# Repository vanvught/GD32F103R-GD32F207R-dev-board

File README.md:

See the latest here -> https://github.com/vanvught/GD32FxxxR-dev-board

-----------

# GD32F103R-GD32F207R-dev-board

This board can be used with the `GD32F103Rx` and the `GD32F207Rx` (Ethernet) MCU's. 

Please note that the crystal for the `GD32F207Rx` is `25MHz` and the crystal for the `GD32F103Rx` is `8MHz`.

The USB is power only.

The 2x13 header is pin compatible with the Orange Pi Zero and Raspberry Pi boards. 

<table>
	<tr><th colspan="6">2x13 Header</th></tr>
	<tr>
	<td colspan="2">3.3V PWR</td>
	<td>1</td>
	<td>2</td>
	<td colspan="2">5V PWR</td>
	</tr>
	<tr>
	<td>I2C0 SCA</td>
	<td>PB7</td>
	<td>3</td>
	<td>4</td>
	<td colspan="2">5V PWR</td>
	</tr>
	<tr>
	<td>I2C0 SCL</td>
	<td>PB6</td>
	<td>5</td>
	<td>6</td>
	<td colspan="2">GND</td>
	</tr>
	<tr>
	<td></td>
	<td>PA6</td>
	<td>7</td>
	<td>8</td>
	<td>PC10</td>
	<td>USART2 TX</td>
	</tr>
	<tr>
	<td colspan="2">GND</td>
	<td>9</td>
	<td>10</td>
	<td>PC11</td>
	<td>USART2 RX</td>
	</tr>
	<tr>
	<td>USART5 RX</td>
	<td>PC7</td>
	<td>11</td>
	<td>12</td>
	<td>PB10</td>
	<td></td>
	</tr>
	<tr>
	<td>USART5 TX</td>
	<td>PC6</td>
	<td>13</td>
	<td>14</td>
	<td colspan="2">GND</td>
	</tr>
	<tr>
	<td></td>
	<td>PB14</td>
	<td>15</td>
	<td>16</td>
	<td>PB15</td>
	<td></td>
	</tr>
	<tr>
	<td colspan="2">3.3V PWR</td>
	<td>17</td>
	<td>18</td>
	<td>PA13</td>
	<td>SWDIO</td>
	</tr>
	<tr>
	<td>SPI2 MOSI</td>
	<td>PB5</td>
	<td>19</td>
	<td>20</td>
	<td colspan="2">GND</td>
	</tr>
	<tr>
	<td>SPI2 MISO</td>
	<td>PB4</td>
	<td>21</td>
	<td>22</td>
	<td>PA11</td>
	<td></td>
	</tr>
	<tr>
	<td>SPI2 SCK</td>
	<td>PB3</td>
	<td>23</td>
	<td>24</td>
	<td>PA15</td>
	<td>SPI2 CS</td>
	</tr>
	<tr>
	<td colspan="2">GND</td>
	<td>25</td>
	<td>26</td>
	<td>PA14</td>
	<td>SWCLK</td>
	</tr>
</table>

<table>
	<tr><th colspan="3">1x13 Header</th></tr>
	<tr>
	<td>1</td>
	<td colspan="2">NC</td>
	</tr>
	<tr>
	<td>2</td>
	<td colspan="2">GND</td>
	</tr>
	<tr>
	<td>3</td>
	<td>PA14</td>
	<td>SWCLK</td>
	</tr>
	<tr>
	<td>4</td>
	<td colspan="2">GND</td>
	</tr>
	<tr>
	<td>5</td>
	<td>PA13</td>
	<td>SWDIO</td>
	</tr>
	<tr>
	<td>6</td>
	<td colspan="2">NRST</td>
	</tr>
	<tr>
	<td>7</td>
	<td>PA5</td>
	<td>DAC1</td>
	</tr>
	<tr>
	<td>8</td>
	<td>PA4</td>
	<td>DAC0</td>
	</tr>
	<tr>
	<td>9</td>
	<td>PC12</td>
	<td>UART4 TX</td>
	</tr>
	<tr>
	<td>10</td>
	<td>PD2</td>
	<td>UART4 RX</td>
	</tr>
	<tr>
	<td>11</td>
	<td colspan="2">NC</td>
	</tr>
	<tr>
	<td>12</td>
	<td>PA3</td>
	<td>ADC</td>
	</tr>
	<tr>
	<td>13</td>
	<td colspan="2">NC</td>
	</tr>
</table>

<table>
	<tr><th colspan="2">USART0 (ISP)</th></tr>
	<tr>
	<td>1</td>
	<td>GND</td>
	</tr>
	<tr>
	<td>2</td>
	<td>RX</td>
	</tr>
	<tr>
	<td>3</td>
	<td>TX</td>
	</tr>	
</table>

<table>
<head>
	<tr>
		<th colspan="2">LED's</th>
	</tr>
</head>
<tbody>
	<tr>
		<td>1</td>
		<td>PC0</td>
	</tr>
	<tr>
		<td>2</td>
		<td>PC2</td>
	</tr>
	<tr>
		<td>3</td>
		<td>PC3</td>
	</tr>
	<tr>
		<td>4</td>
		<td>3V3</td>
	</tr>	
</tbody>
</table>

<table>
	<tr><th colspan="4">2x7 Header</th></tr>
	<tr>
	<td>PB13</td>
	<td>1</td>
	<td>2</td>
	<td>NC</td>
	</tr>
	<tr>
	<td>PB11</td>
	<td>3</td>
	<td>4</td>
	<td>PB12</td>
	</tr>
	<tr>
	<td>PC4</td>
	<td>5</td>
	<td>6</td>
	<td>PC5</td>
	</tr>
	<tr>
	<td>PA1</td>
	<td>7</td>
	<td>8</td>
	<td>PA7</td>
	</tr>
	<tr>
	<td>PA2</td>
	<td>9</td>
	<td>10</td>
	<td>PC1</td>
	</tr>
	<tr>
	<td>GND</td>
	<td>11</td>
	<td>12</td>
	<td>GND</td>
	</tr>
	<tr>
	<td>3V3</td>
	<td>13</td>
	<td>14</td>
	<td>3V3</td>
	</tr>	
</table>

### GD32F207Rx (only)

<table>
<head>
	<tr>
		<th colspan="4">External-PHY</th>
	</tr>
</head>
<tbody>
	<tr>
		<td>RMII TXD1</td>
		<td>1</td>
		<td>2</td>
		<td>NC</td>
	</tr>
	<tr>
		<td>RMII TX_EN</td>
		<td>3</td>
		<td>4</td>
		<td>RMII TXD0</td>
	</tr>
	<tr>
		<td>RMII RXD0</td>
		<td>5</td>
		<td>6</td>
		<td>RMII RXD1</td>
	</tr>
	<tr>
		<td>RMII REF_CLK</td>
		<td>7</td>
		<td>8</td>
		<td>RMII CRS_DV</td>
	</tr>
	<tr>
		<td>MDIO</td>
		<td>9</td>
		<td>10</td>
		<td>MDC</td>
	</tr>
	<tr>
		<td>GND</td>
		<td>11</td>
		<td>12</td>
		<td>GND</td>
	</tr>
	<tr>
		<td>3V3</td>
		<td>13</td>
		<td>14</td>
		<td>3V3</td>
	</tr>		
</tbody>
</table>

[PayPal.Me Donate](https://paypal.me/AvanVught?locale.x=nl_NL)

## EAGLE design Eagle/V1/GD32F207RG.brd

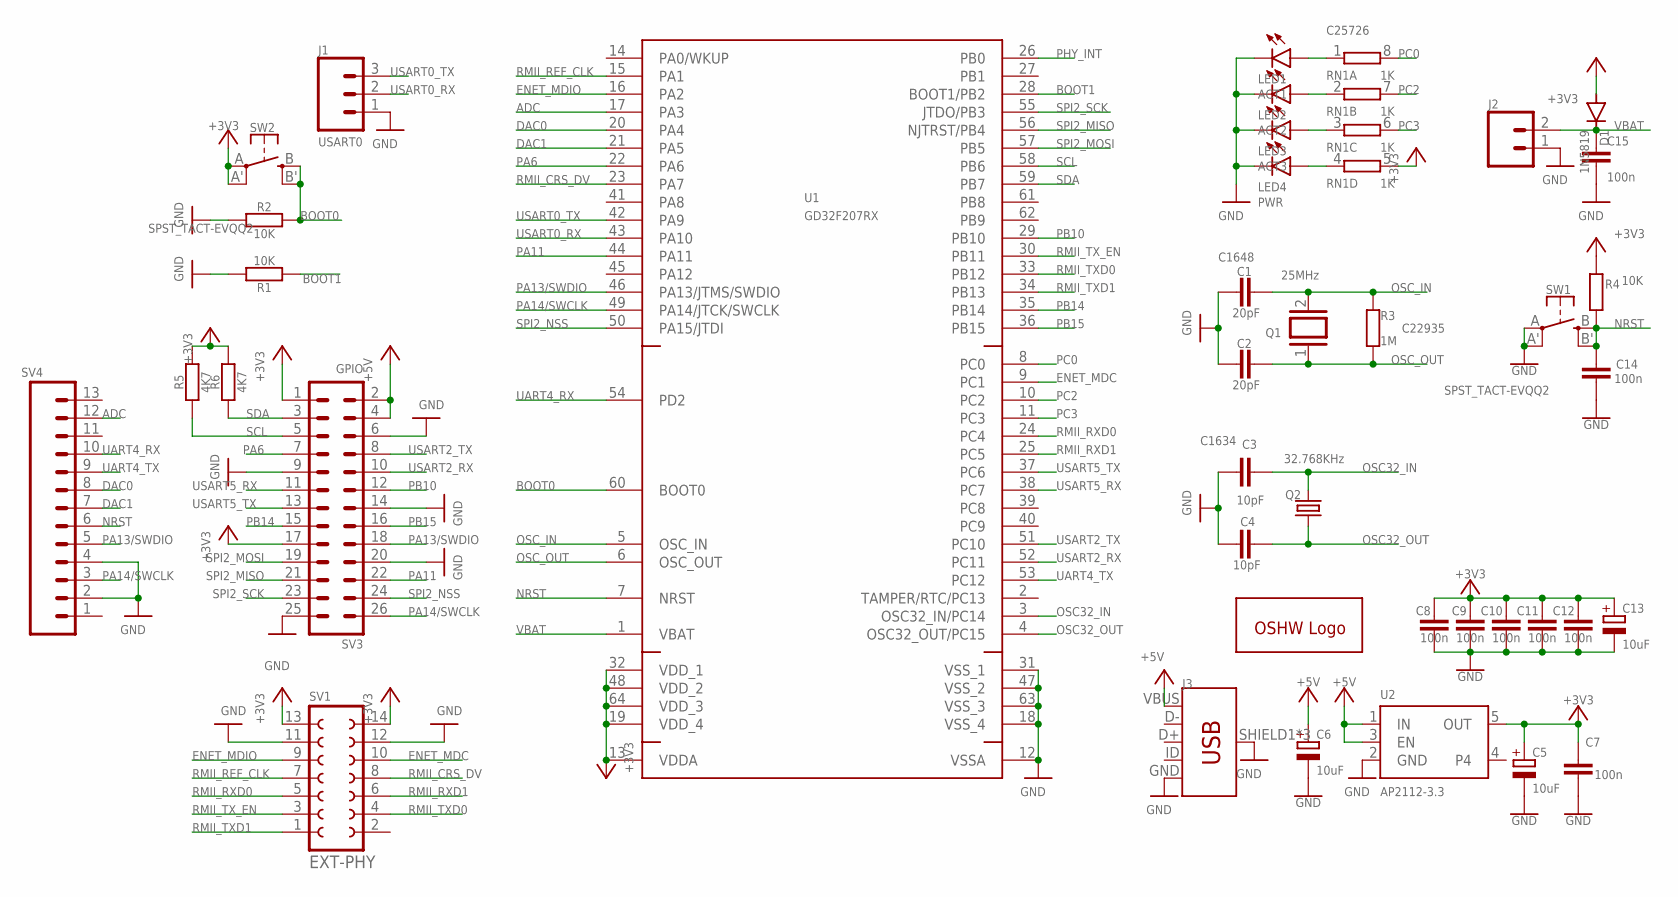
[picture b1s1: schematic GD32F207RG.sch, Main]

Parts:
C1, C2: 20pF; C0603; JLCPCB C1648
C3, C4: 10pF; C0603; JLCPCB C1634
C5, C6, C13: 10uF; A/3216-18R; JLCPCB C7171
C7, C8, C9, C10, C11, C12, C14, C15: 100n; C0603; JLCPCB C14663
D1: 1N5819; SOD323-R; JLCPCB C191023
GOLD_ORB_SM1: OSHWLOGOLOGO5MM; OSHW_5MM
J1: USART0; 1X03
J2: CONN_02JST-PTH-2; JST-2-PTH
J3: USB_MICRO-B_FEMALE-SMT; USB-B-MICRO-SMD; JLCPCB C404968
LED1: ACT1; CHIP-LED0603
LED2: ACT2; CHIP-LED0603
LED3: ACT3; CHIP-LED0603
LED4: PWR; CHIP-LED0603
Q1: 25MHz; QS
Q2: 32.768KHz; TC26H
R1, R2, R4: 10K; R0603; JLCPCB C25804
R3: 1M; R0603; JLCPCB C22935
R5, R6: 4K7; R0603; JLCPCB C23162
RN1: 1K; 4X0402ARV341; JLCPCB C25726
SV1: EXT-PHY; FE07-2W
SV3: GPIO; MA13-2
SV4: CONN_13; 1X13
SW1, SW2: SPST_TACT-EVQQ2; EVQ-Q2
U1: GD32F207RX; LQFP64
U2: AP2112-3.3; SOT23-5; JLCPCB C51118

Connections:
+3V3: C5.+, C7.1, C8.1, C9.1, C10.1, C11.1, C12.1, C13.+, D1.A, R4.2, R5.2, R6.2, RN1.5 (2), SV1.13, SV1.14, SV3.1, SV3.17, SW2.A, SW2.A' (P1), U1.13 (VDDA), U1.19 (VDD_4), U1.32 (VDD_1), U1.48 (VDD_2), U1.64 (VDD_3), U2.5 (OUT)
+5V: C6.+, J3.VBUS, SV3.2, SV3.4, U2.1 (IN), U2.3 (EN)
ADC: SV4.12, U1.17 (PA3)
BOOT0: R2.2, SW2.B (S), SW2.B' (S1), U1.60 (BOOT0)
BOOT1: R1.1, U1.28 (BOOT1/PB2)
DAC0: SV4.8, U1.20 (PA4)
DAC1: SV4.7, U1.21 (PA5)
ENET_MDC: SV1.10, U1.9 (PC1)
ENET_MDIO: SV1.9, U1.16 (PA2)
GND: C1.1, C2.1, C3.1, C4.1, C5.-, C6.-, C7.2, C8.2, C9.2, C10.2, C11.2, C12.2, C13.-, C14.2, C15.2, J1.1, J2.1, J3.GND, J3.SHIELD1 (SHIELD), J3.SHIELD2 (SHIELD), J3.SHIELD3 (SHIELD), LED1.C, LED2.C, LED3.C, LED4.C, R1.2, R2.1, SV1.11, SV1.12, SV3.6, SV3.9, SV3.14, SV3.20, SV3.25, SV4.2, SV4.4, SW1.A, SW1.A' (P1), U1.12 (VSSA), U1.18 (VSS_4), U1.31 (VSS_1), U1.47 (VSS_2), U1.63 (VSS_3), U2.2 (GND)
unnamed: LED1.A, RN1.1
unnamed: LED2.A, RN1.2 (1)
unnamed: LED3.A, RN1.3 (1)
unnamed: LED4.A, RN1.4 (1)
NRST: C14.1, R4.1, SV4.6, SW1.B (S), SW1.B' (S1), U1.7 (NRST)
OSC32_IN: C3.2, Q2.2, U1.3 (OSC32_IN/PC14)
OSC32_OUT: C4.2, Q2.1, U1.4 (OSC32_OUT/PC15)
OSC_IN: C1.2, Q1.2, R3.2, U1.5 (OSC_IN)
OSC_OUT: C2.2, Q1.1, R3.1, U1.6 (OSC_OUT)
PA6: SV3.7, U1.22 (PA6)
PA11: SV3.22, U1.44 (PA11)
PA13/SWDIO: SV3.18, SV4.5, U1.46 (PA13/JTMS/SWDIO)
PA14/SWCLK: SV3.26, SV4.3, U1.49 (PA14/JTCK/SWCLK)
PB10: SV3.12, U1.29 (PB10)
PB14: SV3.15, U1.35 (PB14)
PB15: SV3.16, U1.36 (PB15)
PC0: RN1.8 (2), U1.8 (PC0)
PC2: RN1.7 (2), U1.10 (PC2)
PC3: RN1.6 (2), U1.11 (PC3)
PHY_INT: U1.26 (PB0)
RMII_CRS_DV: SV1.8, U1.23 (PA7)
RMII_REF_CLK: SV1.7, U1.15 (PA1)
RMII_RXD0: SV1.5, U1.24 (PC4)
RMII_RXD1: SV1.6, U1.25 (PC5)
RMII_TXD0: SV1.4, U1.33 (PB12)
RMII_TXD1: SV1.1, U1.34 (PB13)
RMII_TX_EN: SV1.3, U1.30 (PB11)
SCL: R5.1, SV3.5, U1.58 (PB6)
SDA: R6.1, SV3.3, U1.59 (PB7)
SPI2_MISO: SV3.21, U1.56 (NJTRST/PB4)
SPI2_MOSI: SV3.19, U1.57 (PB5)
SPI2_NSS: SV3.24, U1.50 (PA15/JTDI)
SPI2_SCK: SV3.23, U1.55 (JTDO/PB3)
UART4_RX: SV4.10, U1.54 (PD2)
UART4_TX: SV4.9, U1.53 (PC12)
USART0_RX: J1.2, U1.43 (PA10)
USART0_TX: J1.3, U1.42 (PA9)
USART2_RX: SV3.10, U1.52 (PC11)
USART2_TX: SV3.8, U1.51 (PC10)
USART5_RX: SV3.11, U1.38 (PC7)
USART5_TX: SV3.13, U1.37 (PC6)
VBAT: C15.1, D1.C, J2.2, U1.1 (VBAT)

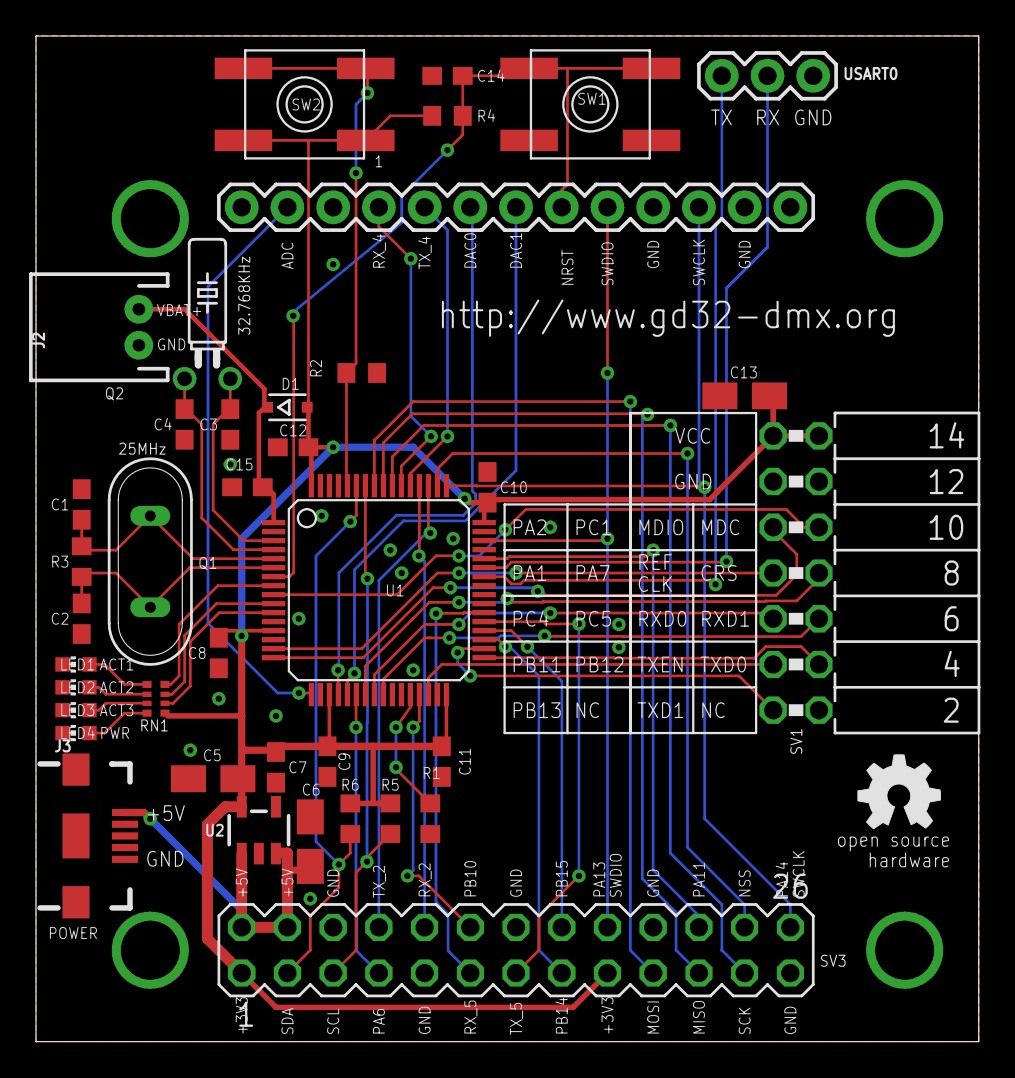
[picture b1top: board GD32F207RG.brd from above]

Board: 2 copper layers, 52.4 x 55.9 mm, 40 parts (0 on the bottom side), 51 nets.

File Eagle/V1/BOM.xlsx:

Qty | Designator | Footprint | Comment | LCSC Part #
2 | C1, C2 | C0603 | 20pF | C1648
2 | C3, C4 | C0603 | 10pF | C1634
3 | C5, C6, C13 | A/3216-18R | 10uF | C7171
8 | C7, C8, C9, C10, C11, C12, C14, C15 | C0603 | 100n | C14663
4 | LED1, LED2, LED3, LED4 | CHIP-LED0603 | LEDCHIP-LED0603 | C72043
1 | D1 | SOD323-R | 1N5819 | C191023
3 | R1, R2, R4 | R0603 | 10K | C25804
2 | R5,R6 | R0603 | 4K7 | C23162
1 | R3 | R0603 | 1M | C22935
1 | RN1 | 4X0402ARV341 | 1K | C25726
1 | U2 | SOT23-5 | TPRT9013-33GB | C587158
1 | J3 | USB_MICRO-B_FEMALE-SMT | USB-B-MICRO-SMD | C404968
29

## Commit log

2021-12-10 V1
    Improvements for next version:
    *. Add USB ISP support
    *. Make SPI NSS configurable
    *. Change USART0 (no REMAP) to BOOT_RX, BOOT_TX
    *. Add USART0 REMAP to single row GPIO header
    *. Improve schematic layout.
2021-12-10 Fixed issue with HTML tables
2021-12-10 Added board picture
2022-02-11 https://github.com/vanvught/GD32FxxxR-dev-board

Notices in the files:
parts and their libraries:
SparkFun-Connectors: Licensing: Creative Commons ShareAlike 4.0 International - https://creativecommons.org/licenses/by-sa/4.0
microbuilder: This work is placed in the public domain, and may be freely used for commercial and non-commercial work with the following conditions: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
